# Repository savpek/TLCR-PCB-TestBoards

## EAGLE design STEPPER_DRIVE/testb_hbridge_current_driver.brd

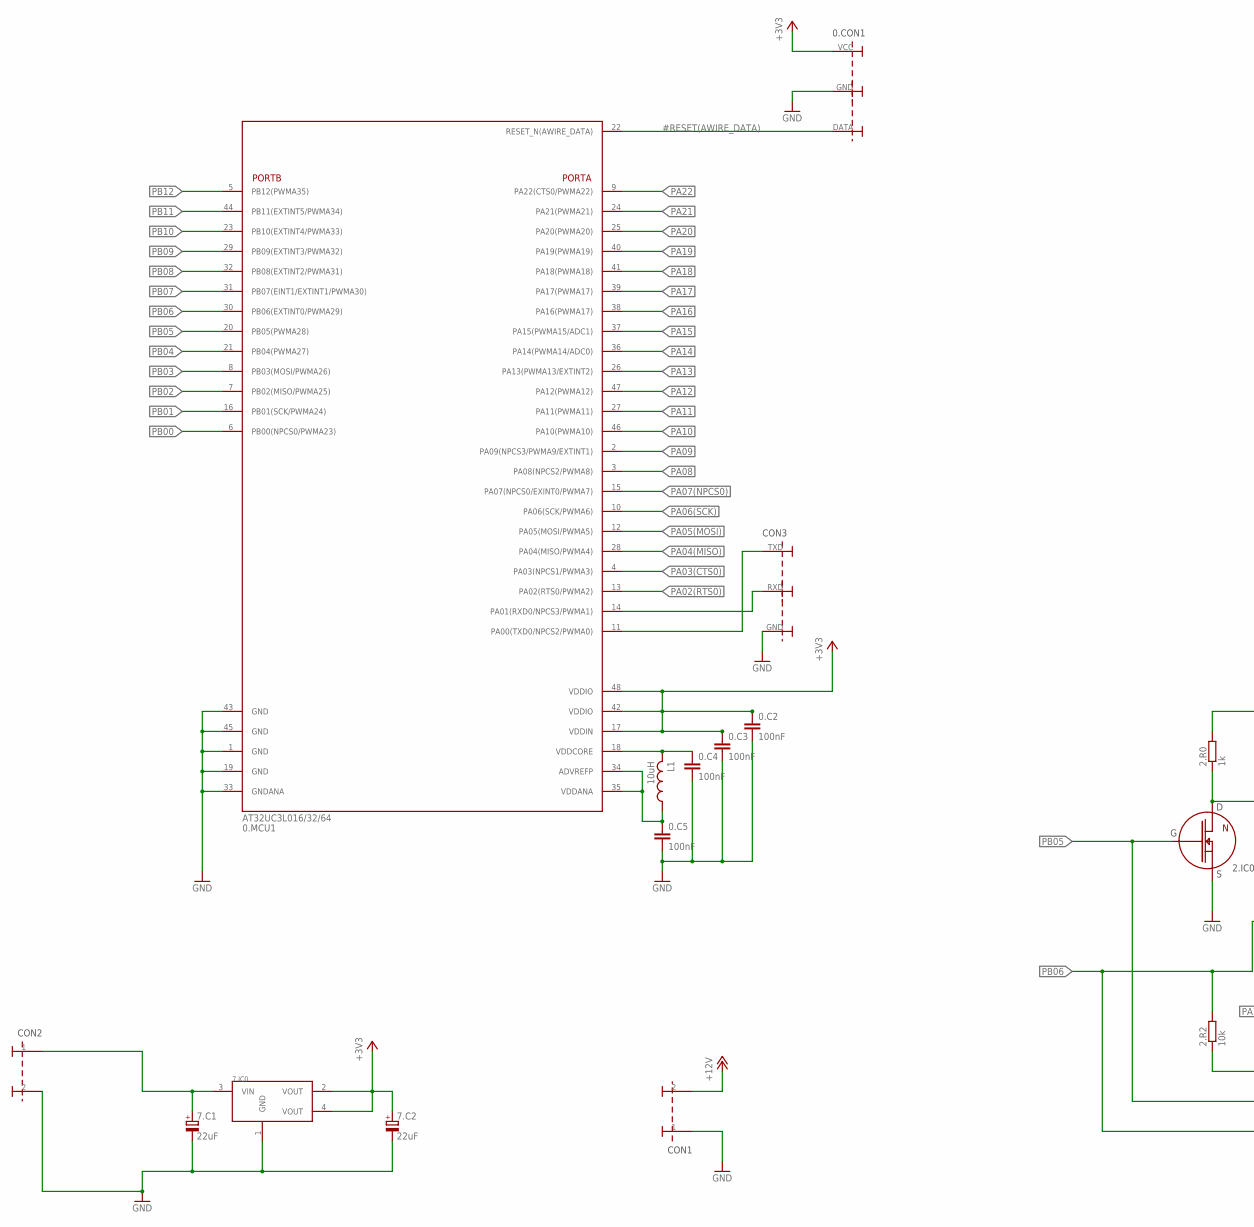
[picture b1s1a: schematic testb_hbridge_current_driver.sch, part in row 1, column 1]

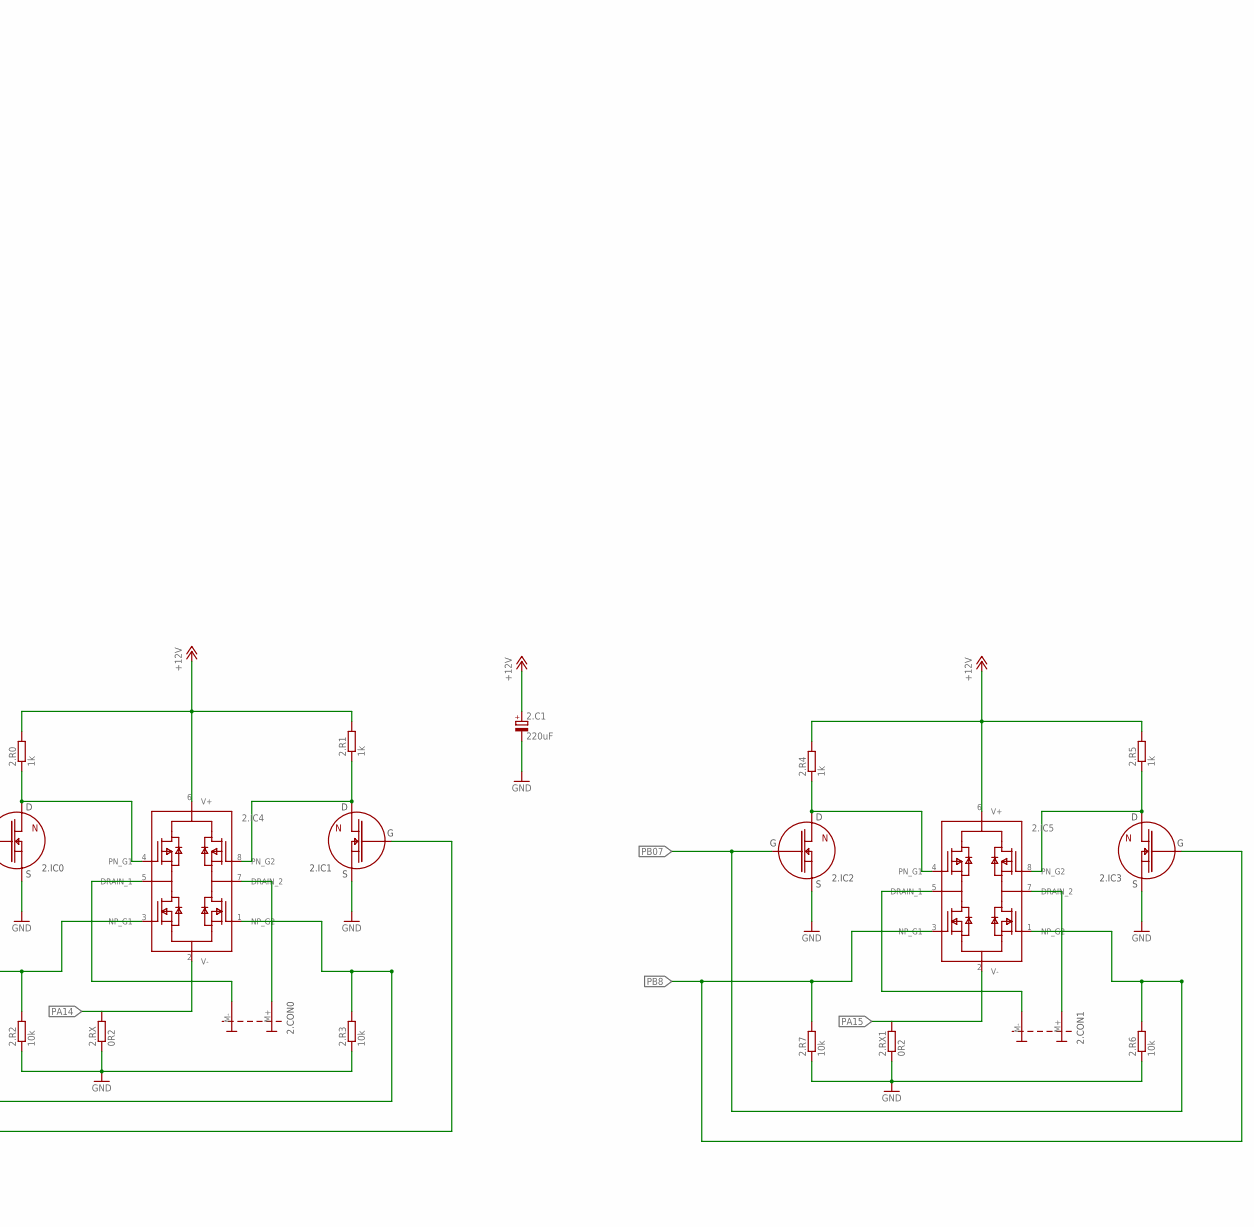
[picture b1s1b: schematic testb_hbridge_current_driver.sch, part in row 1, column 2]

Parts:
0.C2, 0.C3, 0.C4, 0.C5: 100nF; C0805
0.CON1: CONNECTOR_3PINAWIRE; 1X3_AWIRE
0.MCU1: AT32UCL016/32/64_TQFP48; TQFP48
2.C1: 220uF; E3,5-8
2.CON0, 2.CON1: CONNECTOR_2PIN1X2_MOTOR_COIL; 1X2_MOTOR_COIL_CONNECTOR
2.IC0, 2.IC1, 2.IC2, 2.IC3: N_MOSFET_TSM2N7002; SOT23
2.IC4, 2.IC5: ZXMHC6A07T8
2.R0, 2.R1, 2.R4, 2.R5: 1k; R0805
2.R2, 2.R3, 2.R6, 2.R7: 10k; R0805
2.RX, 2.RX1: 0R2; R2010
7.C1, 7.C2: 22uF; E1.5-5
7.IC0: REGULATOR_AP1117E33G-13; SOT223
CON1, CON2: CONNECTOR_2PIN1X2_WIRE; 1X2_WIRE
CON3: CONNECTOR_3PINUSART; 1X3_USART
L1: 10uH; C0805

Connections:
#RESET(AWIRE_DATA): 0.CON1.DATA, 0.MCU1.22 (RESET_N(AWIRE_DATA))
+3V3: 0.C2.1, 0.C3.1, 0.CON1.VCC, 0.MCU1.17 (VDDIN), 0.MCU1.42 (VDDIO), 0.MCU1.48 (VDDIO), 7.C2.+, 7.IC0.2 (VOUT), 7.IC0.4 (VOUT)
+12V: 2.C1.+, 2.IC4.6 (V+), 2.IC5.6 (V+), 2.R0.2, 2.R1.2, 2.R4.2, 2.R5.2, CON1.2
GND: 0.C2.2, 0.C3.2, 0.C4.2, 0.C5.2, 0.CON1.GND, 0.MCU1.1 (GND), 0.MCU1.19 (GND), 0.MCU1.33 (GNDANA), 0.MCU1.43 (GND), 0.MCU1.45 (GND), 2.C1.-, 2.IC0.2 (S), 2.IC1.2 (S), 2.IC2.2 (S), 2.IC3.2 (S), 2.R2.1, 2.R3.1, 2.R6.1, 2.R7.1, 2.RX.1, 2.RX1.1, 7.C1.-, 7.C2.-, 7.IC0.1 (GND), CON1.1, CON2.2, CON3.GND
unnamed: 7.C1.+, 7.IC0.3 (VIN), CON2.1
unnamed: 2.IC0.3 (D), 2.IC4.4 (PN_G1), 2.R0.1
unnamed: 2.CON0.M+, 2.IC4.7 (DRAIN_2)
unnamed: 2.CON0.M-, 2.IC4.5 (DRAIN_1)
unnamed: 0.C5.1, 0.MCU1.34 (ADVREFP), 0.MCU1.35 (VDDANA), L1.1
unnamed: 0.C4.1, 0.MCU1.18 (VDDCORE), L1.2
unnamed: 2.IC2.3 (D), 2.IC5.4 (PN_G1), 2.R4.1
unnamed: 2.IC1.3 (D), 2.IC4.8 (PN_G2), 2.R1.1
unnamed: 2.IC3.3 (D), 2.IC5.8 (PN_G2), 2.R5.1
unnamed: 2.CON1.M+, 2.IC5.7 (DRAIN_2)
unnamed: 2.CON1.M-, 2.IC5.5 (DRAIN_1)
PA00(TXD0): 0.MCU1.11 (PA00(TXD0/NPCS2/PWMA0)), CON3.TXD
PA01(RXD0): 0.MCU1.14 (PA01(RXD0/NPCS3/PWMA1)), CON3.RXD
PA02(RTS0): 0.MCU1.13 (PA02(RTS0/PWMA2))
PA03(CTS0): 0.MCU1.4 (PA03(NPCS1/PWMA3))
PA04(MISO): 0.MCU1.28 (PA04(MISO/PWMA4))
PA05(MOSI): 0.MCU1.12 (PA05(MOSI/PWMA5))
PA06(SCK): 0.MCU1.10 (PA06(SCK/PWMA6))
PA07(NPCS0): 0.MCU1.15 (PA07(NPCS0/EXINT0/PWMA7))
PA08: 0.MCU1.3 (PA08(NPCS2/PWMA8))
PA09: 0.MCU1.2 (PA09(NPCS3/PWMA9/EXTINT1))
PA10: 0.MCU1.46 (PA10(PWMA10))
PA11: 0.MCU1.27 (PA11(PWMA11))
PA12: 0.MCU1.47 (PA12(PWMA12))
PA13: 0.MCU1.26 (PA13(PWMA13/EXTINT2))
PA14: 0.MCU1.36 (PA14(PWMA14/ADC0)), 2.IC4.2 (V-), 2.RX.2
PA15: 0.MCU1.37 (PA15(PWMA15/ADC1)), 2.IC5.2 (V-), 2.RX1.2
PA16: 0.MCU1.38 (PA16(PWMA17))
PA17: 0.MCU1.39 (PA17(PWMA17))
PA18: 0.MCU1.41 (PA18(PWMA18))
PA19: 0.MCU1.40 (PA19(PWMA19))
PA20: 0.MCU1.25 (PA20(PWMA20))
PA21: 0.MCU1.24 (PA21(PWMA21))
PA22: 0.MCU1.9 (PA22(CTS0/PWMA22))
PB00: 0.MCU1.6 (PB00(NPCS0/PWMA23))
PB01: 0.MCU1.16 (PB01(SCK/PWMA24))
PB02: 0.MCU1.7 (PB02(MISO/PWMA25))
PB03: 0.MCU1.8 (PB03(MOSI/PWMA26))
PB04: 0.MCU1.21 (PB04(PWMA27))
PB05: 0.MCU1.20 (PB05(PWMA28)), 2.IC0.1 (G), 2.IC4.1 (NP_G2), 2.R3.2
PB06: 0.MCU1.30 (PB06(EXTINT0/PWMA29)), 2.IC1.1 (G), 2.IC4.3 (NP_G1), 2.R2.2
PB07: 0.MCU1.31 (PB07(EINT1/EXTINT1/PWMA30)), 2.IC2.1 (G), 2.IC5.1 (NP_G2), 2.R6.2
PB08: 0.MCU1.32 (PB08(EXTINT2/PWMA31))
PB8: 2.IC3.1 (G), 2.IC5.3 (NP_G1), 2.R7.2
PB09: 0.MCU1.29 (PB09(EXTINT3/PWMA32))
PB10: 0.MCU1.23 (PB10(EXTINT4/PWMA33))
PB11: 0.MCU1.44 (PB11(EXTINT5/PWMA34))
PB12: 0.MCU1.5 (PB12(PWMA35))

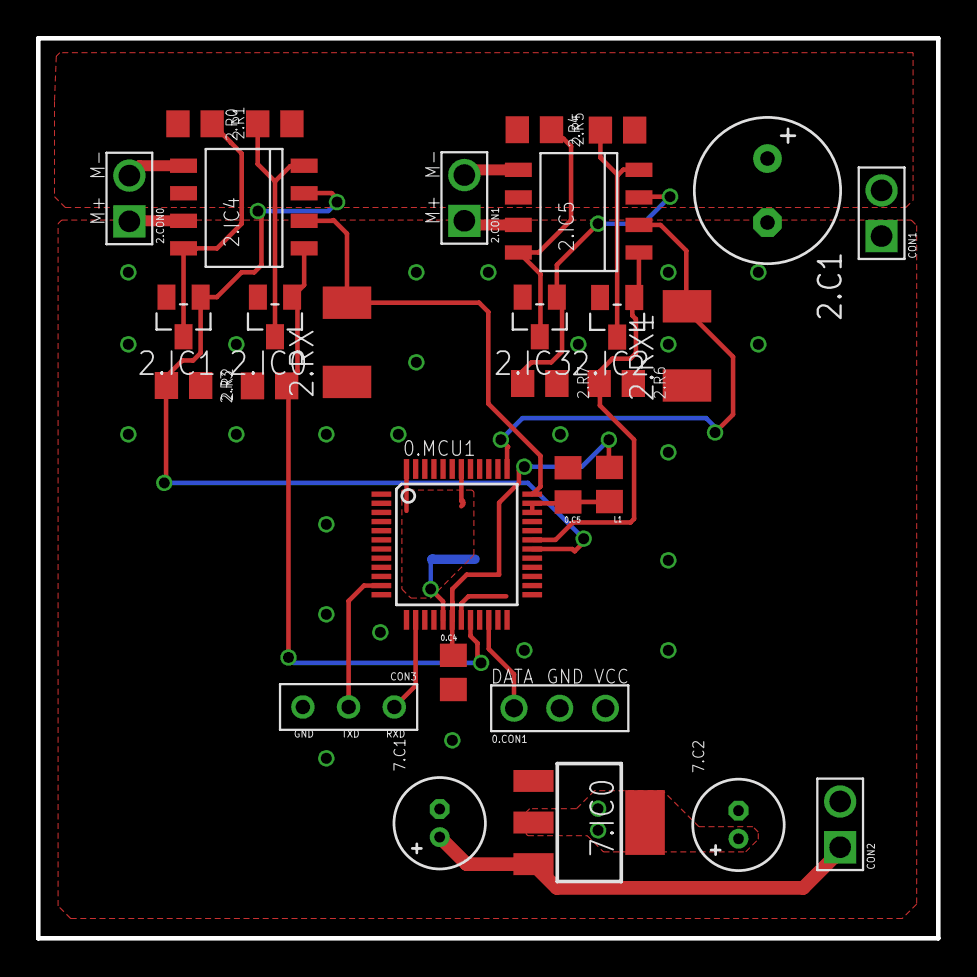
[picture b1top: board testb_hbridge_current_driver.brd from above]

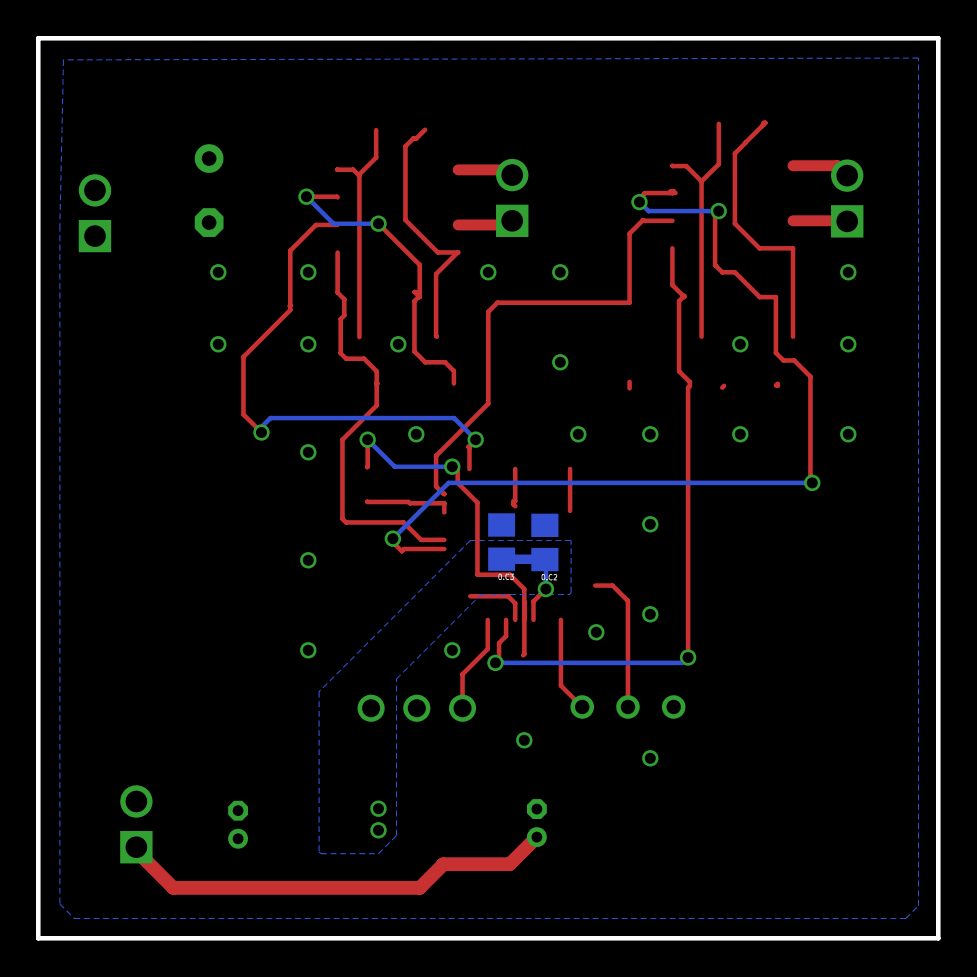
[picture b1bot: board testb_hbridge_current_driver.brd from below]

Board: 2 copper layers, 50.0 x 50.0 mm, 32 parts (2 on the bottom side), 23 nets.

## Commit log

2012-07-27 Initial commit.
